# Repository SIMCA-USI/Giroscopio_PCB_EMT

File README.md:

# Codigo_Vibraciones

Sistema de medición de vibraciones en vehículos EMT usando una PCB con ESP32-C6 y sensor MPU6050.

---

## Estructura del proyecto

```
Codigo_Vibraciones/
├── README.md
├── Datos/                        ← Scripts Python (ejecutar en el PC)
│   ├── logger_plot.py            ← v1: logger básico, 1 dispositivo
│   ├── logger_plot2.py           ← v2: multi-dispositivo, threads
│   ├── logger_plot3.py           ← v3: añade GPS (NMEA) y baseline automático
│   ├── logger_plot4.py           ← v4: versión completa (producción)
│   ├── graficas.py               ← Visor offline de CSVs grabados
│   ├── ruta.py                   ← Genera mapa HTML coloreado por velocidad
│   ├── correlacion.py            ← Sincroniza 2 sensores por correlación cruzada
│   ├── analisis_vibraciones.py   ← Análisis frecuencial (PSD, tercios de octava)
│   └── arreglar_csv_mpu.py       ← Corrector de unidades mal escaladas en CSV
└── vibraciones_EMT/              ← Firmware PlatformIO (para la PCB)
    ├── platformio.ini
    └── src/
        └── main.cpp
```

---

## Hardware

| Componente | Detalle |
|---|---|
| Microcontrolador | ESP32-C6 (RISC-V) |
| Sensor IMU | MPU6050 — acelerómetro ±8g + giroscopio ±250°/s |
| Comunicación con PC | USB Serie a **460800 baudios** |
| I2C | SDA=21, SCL=22, 400 kHz |

---

## Firmware (`vibraciones_EMT/src/main.cpp`)

El firmware mide a **80 Hz** (configurable) y emite por serie una línea CSV por muestra:

```
t_ms, ax_ms2, ay_ms2, az_ms2, gx_dps, gy_dps, gz_dps
```

Al arrancar, emite también:
```
Ubicacion:<nombre>
```

El nombre de ubicación (ej: `"Asiento"`, `"Suelo"`) se configura en `platformio.ini`:

```ini
[env:esp32-c6-devkitm-1]
build_flags = -DUBICACION=\"Asiento\" -DSAMPLE_HZ=80
```

### Comandos serie disponibles

| Comando | Respuesta |
|---|---|
| `WHO\n` | `Ubicacion:<nombre>` |
| `SYNC\n` | `SYNC_OK` |

---

## Scripts Python (`Datos/`)

### `logger_plot4.py` — Logger principal (v4, usar éste)

Graba datos de uno o varios ESP32 simultáneamente, con GPS opcional.

**Configurar antes de ejecutar** (parte superior del fichero):

```python
OUTPUT_DIR = "/ruta/donde/guardar"
BASE_NAME  = "Nombre_de_la_sesion"
SAMPLE_HZ  = 30        # Hz del plot visual
TARGET_LOG_HZ = 30.0   # Hz de guardado en CSV
```

**Columnas del CSV generado:**

```
ubicacion | t_ms | pc_time_s | tiempo_s | ax_ms2 | ay_ms2 | az_ms2 |
gx_dps | gy_dps | gz_dps | gps_lat | gps_lon | gps_alt_m | gps_sats |
gps_fix | gps_hdop | velocidad | sync_time_s | pc_recv_s | segment_id
```

**Ejecutar:**
```bash
python Datos/logger_plot4.py
```

---

### `graficas.py` — Visor offline

Lee uno o varios CSVs ya grabados y muestra una interfaz interactiva con sliders para navegar por la grabación.

**Configurar:**
```python
CSV_PATHS = ["ruta/al/archivo.csv"]
OUTPUT_DIR = "ruta/salida"
```

```bash
python Datos/graficas.py
```

---

### `ruta.py` — Mapa de ruta por velocidad

Genera un HTML interactivo (Folium) con la ruta pintada en colores según velocidad GPS.

```bash
python Datos/ruta.py --csv grabacion.csv --html ruta.html --no-png
```

Rangos de color por defecto: verde 0-10 km/h, amarillo 10-30, rojo >30.

---

### `analisis_vibraciones.py` — Análisis frecuencial completo (v2)

Compara **dos CSVs** (ej: asiento vs suelo del conductor). Complementa a `logger_plot4.py`
realizando en post-proceso el análisis normativo completo que no puede hacerse en tiempo real.

#### Uso básico

```bash
python Datos/analisis_vibraciones.py \
  --csv1 asiento.csv \
  --csv2 suelo.csv \
  --axis z \
  --fmax 80 \
  --out resultados/
```

#### Argumentos completos

| Argumento | Por defecto | Descripción |
|---|---|---|
| `--csv1` | *(obligatorio)* | Primer CSV (ej: asiento del conductor) |
| `--csv2` | *(obligatorio)* | Segundo CSV (ej: suelo de la cabina) |
| `--axis` | `z` | Eje a analizar: `x`, `y` o `z` (vertical = `z`) |
| `--fmax` | `80.0` | Frecuencia máxima de análisis en Hz |
| `--out` | `out_vibraciones` | Directorio de salida |
| `--ref_curve` | — | CSV con curva de referencia (`fc_hz`, `ref`) |
| `--prom` | `1.0` | Prominencia mínima de picos temporales (m/s²) |
| `--min_peak_dist` | `0.30` | Distancia mínima entre picos temporales (s) |
| `--no_iso` | — | Desactiva el análisis ISO 2631-1 |
| `--jerk_window_s` | `1.0` | Ventana RMS deslizante del jerk (s) |
| `--n_peaks` | `10` | Nº máximo de picos espectrales a reportar |

#### Ficheros generados en `--out`

| Fichero | Contenido |
|---|---|
| `time_{eje}.png` | Señal temporal (últimos 60s), ambos CSVs superpuestos |
| `psd_{eje}.png` | PSD Welch — densidad espectral de potencia (m²/s⁴/Hz) |
| `third_octave_{eje}.png` | RMS por bandas de 1/3 de octava (0.5–80 Hz) |
| `ratio_{eje}.png` | Ratio CSV2/CSV1 por banda (transmisibilidad / SEAT) |
| `time_weighted_{eje}.png` | Señal ponderada ISO 2631-1 (Wk o Wd), ambos CSVs |
| `vdv_{eje}.png` | VDV acumulado en el tiempo para ambos CSVs |
| `jerk_{eje}.png` | Jerk (brusquedad) — RMS deslizante de 1s |
| `fft_amplitudes_{eje}.png` | Espectro FFT de amplitudes con picos marcados |
| `third_octave_{eje}.csv` | Tabla de RMS por banda + ratio CSV2/CSV1 |
| `fft_amplitudes_{eje}.csv` | Espectro completo: `freq_hz`, `amplitude_csv1_ms2`, `amplitude_csv2_ms2` |
| `spectral_peaks_csv1_{eje}.csv` | Picos dominantes CSV1: frecuencia, amplitud, prominencia |
| `spectral_peaks_csv2_{eje}.csv` | Picos dominantes CSV2: frecuencia, amplitud, prominencia |
| `summary_{eje}.json` | Resumen completo: fs, offset, RMS total, picos, ISO 2631 |

#### Métricas ISO 2631-1 calculadas (sección `iso2631` del JSON)

| Métrica | Descripción |
|---|---|
| `aw_rms` | RMS de la señal ponderada Wk/Wd (m/s²) |
| `vdv` | Vibration Dose Value total (m/s^1.75) |
| `cf` | Crest Factor — si CF > 9: usar VDV en lugar de RMS |
| `jerk_rms_ms3` | RMS del jerk de toda la señal (m/s³) |
| `jerk_p99_ms3` | Percentil 99 del jerk absoluto (m/s³) |

---

### `arreglar_csv_mpu.py` — Corrector de unidades

Detecta y corrige automáticamente CSVs con datos de aceleración mal escalados (problema de versiones antiguas del firmware).

```bash
python Datos/arreglar_csv_mpu.py grabacion.csv
# Genera: grabacion_fixed.csv
```

---

### `correlacion.py` — Sincronización de sensores

Estima el desfase temporal entre dos grabaciones simultáneas (de distinto ESP32) mediante correlación cruzada. Actualmente tiene las rutas hardcodeadas; editar directamente el archivo para apuntarlas a los CSVs deseados.

---

## Flujo de trabajo típico

```
1. Conectar ESP32(s) y GPS (opcional) por USB
2. Ejecutar logger_plot4.py
3. Recoger datos → se genera CSV automáticamente
4. Analizar con graficas.py / analisis_vibraciones.py / ruta.py
```

---

## Dependencias Python

```bash
pip install pyserial matplotlib pandas numpy scipy folium
```

> Para exportar PNG desde `ruta.py` también se necesita: `pip install selenium webdriver-manager`

---

## Notas

- Las rutas de salida (`OUTPUT_DIR`) en todos los scripts apuntan a `/home/adrian/...` (entorno Linux de desarrollo). **Deben cambiarse** antes de ejecutar.
- El baseline (sesgo DC del sensor) se calcula automáticamente con las primeras 200 muestras. Los datos se guardan **con baseline ya sustraído**.
- Si usas varias PCBs a la vez, cada una debe tener diferente `UBICACION` configurada en su `platformio.ini`.

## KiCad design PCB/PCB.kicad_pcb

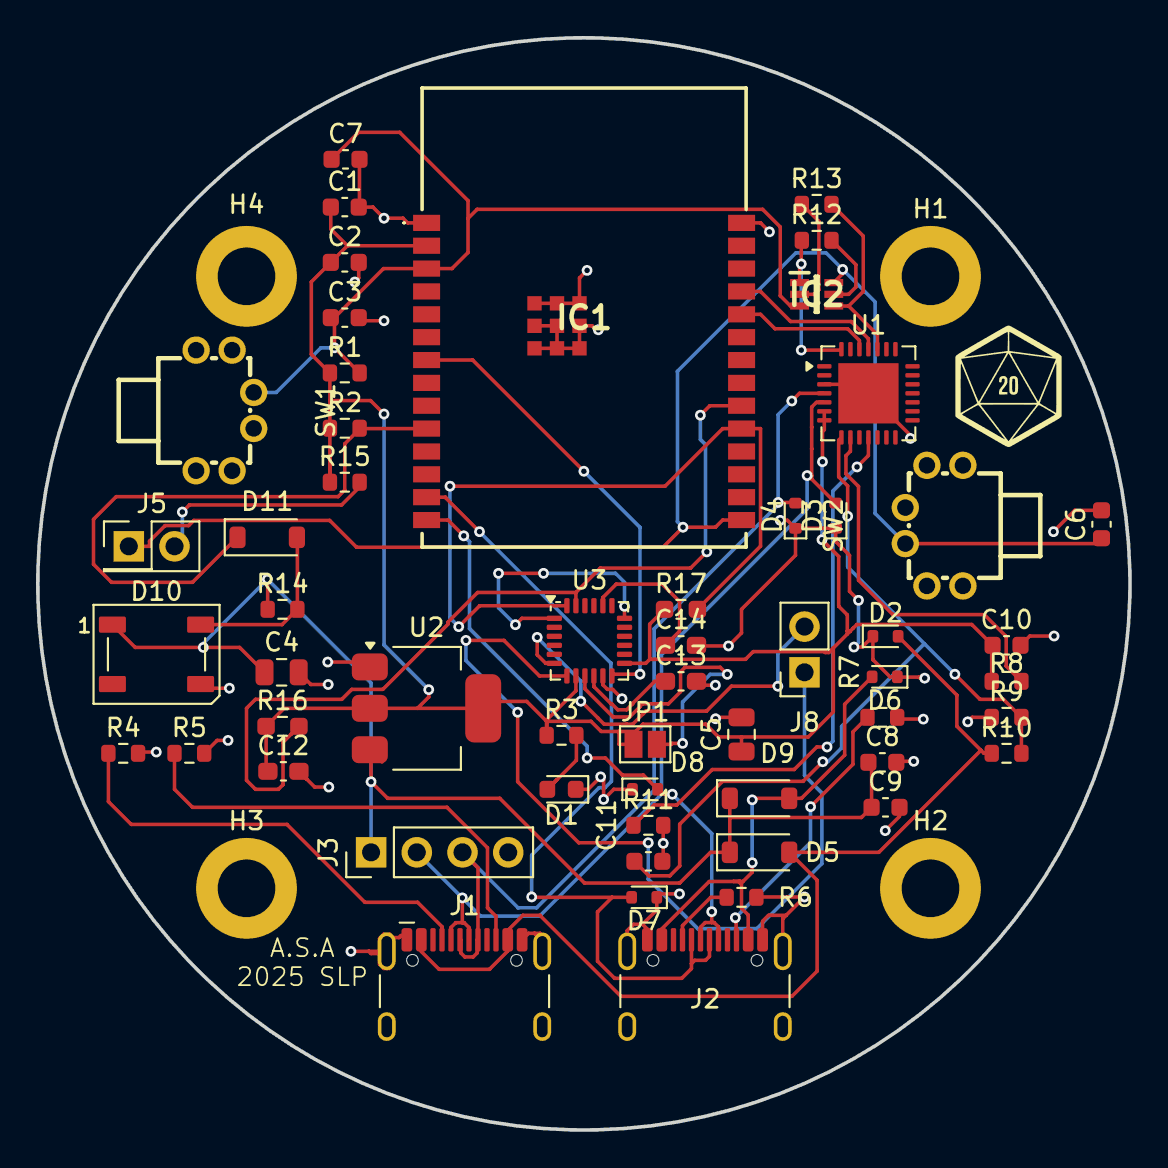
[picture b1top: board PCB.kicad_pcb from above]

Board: 2 copper layers, 60.7 x 60.7 mm, 61 parts (1 on the bottom side), 36 nets.

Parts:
C1, C8, C9, C10: 10μF. 25V. 20%; C_0603_1608Metric
C2, C6, C7: 0.1μF. 50V. 10%; C_0603_1608Metric
C3, C11: 1μF. 16V. 10%; C_0603_1608Metric
C4: 10μF. 50V; C_0805_2012Metric
C5: 22μF 25V; C_0805_2012Metric
C12: 0.1uF 4V; C_0603_1608Metric_Pad1.08x0.95mm_HandSolder
C13: 0.1uF 2V; C_0603_1608Metric_Pad1.08x0.95mm_HandSolder
C14: 2.2nF 50V; C_0603_1608Metric_Pad1.08x0.95mm_HandSolder
D1: LED; LED_0603_1608Metric
D2, D3, D4, D6, D7, D8: D_TVS; D_SOD-523
D5, D9: 1N5819; D_SOD-123
D10: WS2812B; LED_WS2812B_PLCC4_5.0x5.0mm_P3.2mm
D11: 1N4148W; D_SOD-123
G1, G2: LOGO
H1, H2, H3, H4: MountingHole_Pad; MountingHole_3.2mm_M3_DIN965_Pad
IC1: ESP32-C6-WROOM-1-N8; ESP32C6WROOM1N8
IC2: SOT65P210X110-6N
J1, J2: USB_C_Receptacle_USB2.0_14P; USB_C_Receptacle_HCTL_HC-TYPE-C-16P-01A
J3: Conn_01x04; PinHeader_1x04_P2.54mm_Vertical
J5: Jumper CAN; PinHeader_2x01_P2.54mm_Vertical
J8: Aux_IMU; PinSocket_1x02_P2.54mm_Vertical
JP1: I2C_add; SolderJumper-2_P1.3mm_Open_Pad1.0x1.5mm
R1, R2, R11, R12, R13: 10k. 1%; R_0603_1608Metric
R3, R4, R5, R6, R7: 5.1k; R_0603_1608Metric
R8: 1k. 1%; R_0603_1608Metric
R9: 47.5k. 1%; R_0603_1608Metric
R10: 22.1k. 1%; R_0603_1608Metric
R14: 4.7K. 1%; R_0603_1608Metric
R15: 47K. 1%; R_0603_1608Metric
R16, R17: 10K; R_0603_1608Metric_Pad0.98x0.95mm_HandSolder
SW1, SW2: TK-6580A8-1; SW-TH_TK-6580A8-1
U1: CP2102N-Axx-xQFN28; QFN-28-1EP_5x5mm_P0.5mm_EP3.35x3.35mm
U2: AMS1117-3.3; SOT-223-3_TabPin2
U3: MPU-6050; InvenSense_QFN-24_4x4mm_P0.5mm

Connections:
3.3V: C1.1, C2.1, C5.1, C10.1, C12.1, IC1.2 (3V3), JP1.1 (A), R1.1, R2.1, R3.1, R8.1, R15.1, R16.1, R17.1, U1.6 (VDD), U1.7 (VREGIN), U2.2 (VO), U3.8 (VLOGIC), U3.13 (VDD)
5V: C4.1, C8.1, C9.1, D5.1 (K), D9.1 (K), D10.1 (VDD), J3.1, R14.1, U2.3 (VI)
/RGB_CRTL: D10.4 (DIN), D11.2 (A), R14.2
AUX_CL: J8.1, U3.7 (AUX_CL)
AUX_DA: J8.2, U3.6 (AUX_DA)
CHIP_PU: C3.1, C7.1, IC1.3 (EN), IC2.3 (C1), R1.2, SW1.6
DTR: IC2.1 (E2), R12.1, U1.28 (~DTR)
GND: C1.2, C2.2, C3.2, C4.2, C5.2, C6.2, C7.2, C8.2, C9.2, C10.2, C11.2, C12.2, C13.2, C14.2, D1.1 (K), D2.1 (A1), D3.1 (A1), D4.1 (A1), D6.1 (A1), D7.1 (A1), D8.1 (A1), D10.3 (VSS), H1.1, H2.1, H3.1, H4.1, IC1.1 (GND_1), IC1.28 (GND_2), IC1.29 (GND_3), IC1.30 (GND_4), IC1.31 (GND_5), IC1.32 (GND_6), IC1.33 (GND_7), IC1.34 (GND_8), IC1.35 (GND_9), IC1.36 (GND_10), IC1.37 (GND_11), J1.A1 (GND), J1.A12 (GND), J1.B1 (GND), J1.B12 (GND), J1.S1 (SHIELD), J2.A1 (GND), J2.A12 (GND), J2.B1 (GND), J2.B12 (GND), J2.S1 (SHIELD), J3.4, R4.2, R5.2, R6.2, R7.2, R9.1, R11.2, SW1.1, SW2.1, U1.3 (GND), U1.29 (GND), U2.1 (GND), U3.1 (CLKIN), U3.11 (FSYNC), U3.18 (GND)
GPIO8: D11.1 (K), IC1.10 (IO8), R2.2
GPIO9: C6.1, IC1.15 (IO9), IC2.6 (C2), J5.1, SW2.6
GPIO12: D7.2 (A2), IC1.13 (IO12), J2.A7 (D-), J2.B7 (D-)
GPIO13: D8.2 (A2), IC1.14 (IO13), J2.A6 (D+), J2.B6 (D+)
IMU_INT: IC1.7 (IO7), U3.12 (INT)
unnamed: D1.2 (A), R3.2
unnamed: IC2.5 (B1), R12.2
unnamed: IC2.2 (B2), R13.1
unnamed: J1.A5 (CC1), R4.1
unnamed: J1.B5 (CC2), R5.1
unnamed: J2.A5 (CC1), R6.1
unnamed: J2.B5 (CC2), R7.1
unnamed: J5.2, R15.2
unnamed: JP1.2 (B), U3.9 (AD0)
unnamed: C11.1, R9.2, R10.2, U1.8 (VBUS)
unnamed: R8.2, U1.9 (~RST)
unnamed: R11.1, U1.11 (~SUSPEND)
unnamed: C14.1, U3.20 (CPOUT)
unnamed: C13.1, U3.10 (REGOUT)
RTS: IC2.4 (E1), R13.2, U1.24 (~RTS)
SCL: IC1.20 (IO22), R16.2, U3.23 (SCL)
SDA: IC1.19 (IO21), R17.2, U3.24 (SDA)
UART_RXD: IC1.24 (RXD0), U1.26 (TXD)
UART_TXD: IC1.25 (TXD0), U1.25 (RXD)
USB_D+: D4.2 (A2), J1.A6 (D+), J1.B6 (D+), J3.3, U1.4 (D+)
USB_D-: D3.2 (A2), J1.A7 (D-), J1.B7 (D-), J3.2, U1.5 (D-)
VBUSA: D2.2 (A2), D5.2 (A), J1.A4 (VBUS), J1.A9 (VBUS), J1.B4 (VBUS), J1.B9 (VBUS), R10.1
VBUSB: D6.2 (A2), D9.2 (A), J2.A4 (VBUS), J2.A9 (VBUS), J2.B4 (VBUS), J2.B9 (VBUS)

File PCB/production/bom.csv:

Designator,Footprint,Quantity,Value,LCSC Part #
"C1, C10, C8, C9",603,4,10μF. 25V. 20%,C96446
"C11, C3",603,2,1μF. 16V. 10%,C15849
C12,603,1,0.1uF 4V,C1590
C13,603,1,0.1uF 2V,C1590
C14,603,1,2.2nF 50V,C1604
"C2, C6, C7",603,3,0.1μF. 50V. 10%,C14663
C4,805,1,10μF. 50V,C440198
C5,805,1,22μF 25V,C45783
D1,603,1,LED,C2286
D10,LED_WS2812B_PLCC4_5.0x5.0mm_P3.2mm,1,WS2812B,C2843785
D11,D_SOD-123,1,1N4148W,C7420318
"D2, D3, D4, D6, D7, D8",D_SOD-523,6,D_TVS,C5199850
"D5, D9",D_SOD-123,2,1N5819,C82544
IC1,ESP32C6WROOM1N8,1,ESP32-C6-WROOM-1-N8,C5366877
IC2,SOT65P210X110-6N,1,~,C82368
"J1, J2",USB_C_Receptacle_HCTL_HC-TYPE-C-16P-01A,2,USB_C_Receptacle_USB2.0_14P,C165948
"R1, R11, R12, R13, R2",603,5,10k. 1%,C25804
R10,603,1,22.1k. 1%,C31850
R14,603,1,4.7K. 1%,C31850
R15,603,1,47K. 1%,C21189
"R16, R17",603,2,10K,C25804
"R3, R4, R5, R6, R7",603,5,5.1k,C23186
R8,603,1,1k. 1%,C21190
R9,603,1,47.5k. 1%,C25819
"SW1, SW2",SW-TH_TK-6580A8-1,2,TK-6580A8-1,C528772
U1,QFN-28-1EP_5x5mm_P0.5mm_EP3.35x3.35mm,1,CP2102N-Axx-xQFN28,C964632
U2,SOT-223-3_TabPin2,1,AMS1117-3.3,C347222
U3,InvenSense_QFN-24_4x4mm_P0.5mm,1,MPU-6050,C24112

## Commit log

2025-12-02 PCB y production
2025-12-02 Produccion acabada
2025-12-02 Se incorpora logo y se regeneran ficheros de producción
2025-12-11 codigo esp32 hecho
2025-12-11 acelerometro da respuesta pero erronea
2025-12-15 primeros pasos con una ESP32
2025-12-15 Arreglo codigo platformIO con calibracion del eje Z a 0g
2025-12-15 Giroscopio V1 con pruebas aceptables y correctas
2025-12-16 V1 con timestamp
2025-12-16 V2 para varias PCBs funcional
2025-12-18 V3 con gps sin velocidad en Tiempo Real
2025-12-18 Arreglo GPS en logger_plot3 y codigo para resultados en graficas
2026-01-13 Cambios nombres graficas de resultados para mas claridad
2026-02-24 version 4 del proyecto
2026-02-27 arreglo de códigos con mejor eficiencia
2026-02-27 readme actualizado
